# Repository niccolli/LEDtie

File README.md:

# About
Arduino remote controlling system from iPhone. Between iPhone and Arduino, there is a Node.js server. Communicating iPhone and Node.js on WebSocket, Node.js and Arduino on XBee.

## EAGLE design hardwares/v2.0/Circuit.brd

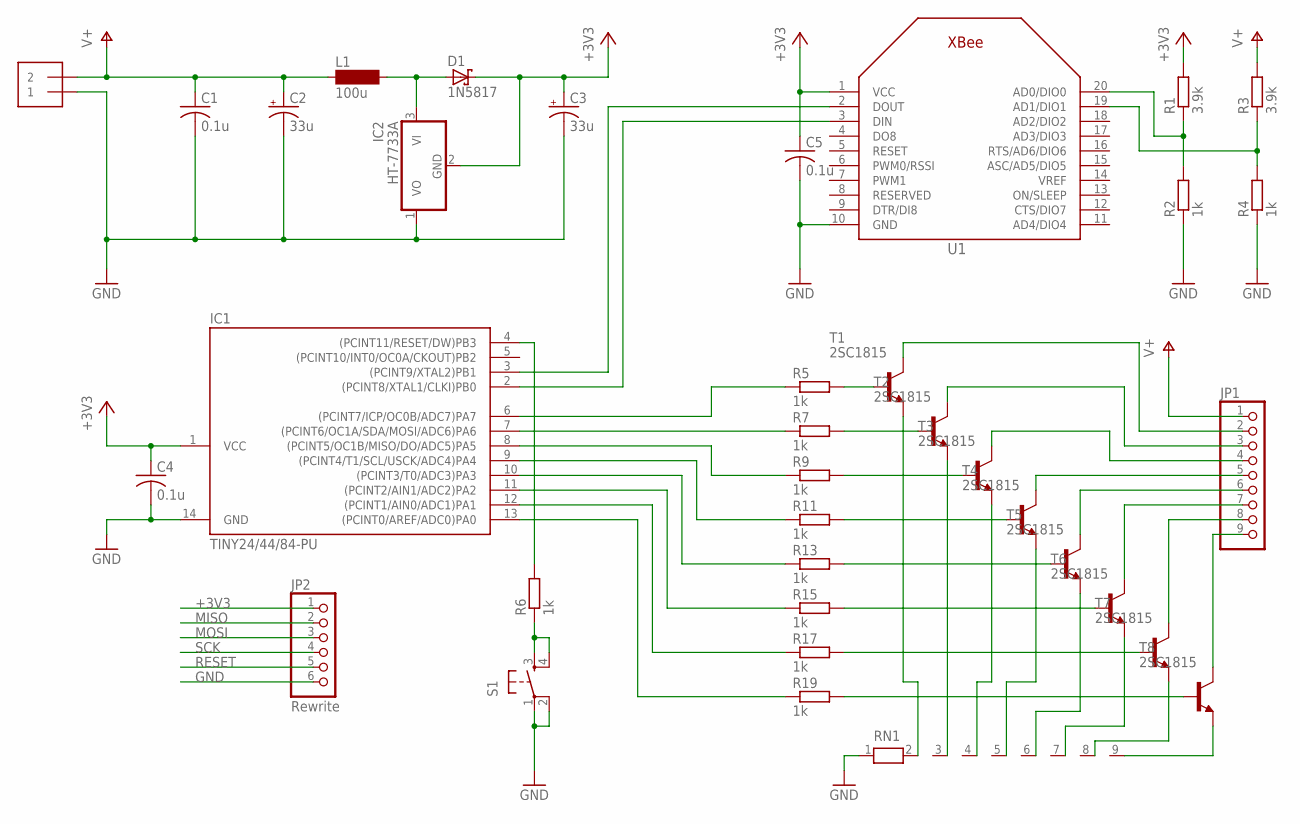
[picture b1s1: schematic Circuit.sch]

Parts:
C1, C4, C5: 0.1u; C050-025X075
C2, C3: 33u; E2,5-6
D1: 1N5817; DO41-7
IC1: TINY24/44/84-PU; DIL14
IC2: HT-7733A; TO92
J1: 1X2-3.5MM
JP1: PINHD-1X9; 1X09-BIG
JP2: Rewrite; 1X06
L1: 100u; BS11
R1, R3: 3.9k; 0204/7
R2, R4, R5, R6, R7, R9, R11, R13, R15, R17, R19: 1k; 0204/7
RN1: RN08; RN-9
S1: TAC_SWITCHPTH; TACTILE-PTH
T1, T2, T3, T4, T5, T6, T7, T8: 2SC1815; TO92-ECB
U1: XBEE

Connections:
+3V3: C3.+, C4.1, C5.1, D1.C, IC1.1 (VCC), IC2.2 (GND), JP2.1, R1.2, U1.1 (VCC)
GND: C1.2, C2.-, C3.-, C4.2, C5.2, IC1.14 (GND), IC2.1 (VO), J1.1, JP2.6, R2.1, R4.1, RN1.1, S1.1, S1.2, U1.10 (GND)
MISO: IC1.8 ((PCINT5/OC1B/MISO/DO/ADC5)PA5), JP2.2, R9.1
MOSI: IC1.7 ((PCINT6/OC1A/SDA/MOSI/ADC6)PA6), JP2.3, R7.1
unnamed: IC1.3 ((PCINT9/XTAL2)PB1), U1.2 (DOUT)
unnamed: IC1.2 ((PCINT8/XTAL1/CLKI)PB0), U1.3 (DIN)
unnamed: D1.A, IC2.3 (VI), L1.2
unnamed: R6.1, S1.3, S1.4
unnamed: R5.2, T1.B
unnamed: JP1.2, T1.C
unnamed: R1.1, R2.2, U1.20 (AD0/DIO0)
unnamed: R3.1, R4.2, U1.19 (AD1/DIO1)
unnamed: R7.2, T2.B
unnamed: JP1.3, T2.C
unnamed: IC1.6 ((PCINT7/ICP/OC0B/ADC7)PA7), R5.1
unnamed: R9.2, T3.B
unnamed: JP1.4, T3.C
unnamed: RN1.8, T7.E
unnamed: R11.2, T4.B
unnamed: JP1.5, T4.C
unnamed: R13.2, T5.B
unnamed: JP1.6, T5.C
unnamed: R15.2, T6.B
unnamed: JP1.7, T6.C
unnamed: IC1.10 ((PCINT3/T0/ADC3)PA3), R13.1
unnamed: R17.2, T7.B
unnamed: JP1.8, T7.C
unnamed: IC1.11 ((PCINT2/AIN1/ADC2)PA2), R15.1
unnamed: R19.2, T8.B
unnamed: JP1.9, T8.C
unnamed: IC1.12 ((PCINT1/AIN0/ADC1)PA1), R17.1
unnamed: RN1.3, T2.E
unnamed: RN1.4, T3.E
unnamed: RN1.5, T4.E
unnamed: RN1.6, T5.E
unnamed: RN1.7, T6.E
unnamed: RN1.9, T8.E
unnamed: RN1.2, T1.E
unnamed: IC1.13 ((PCINT0/AREF/ADC0)PA0), R19.1
RESET: IC1.4 ((PCINT11/RESET/DW)PB3), JP2.5, R6.2
SCK: IC1.9 ((PCINT4/T1/SCL/USCK/ADC4)PA4), JP2.4, R11.1
V+: C1.1, C2.+, J1.2, JP1.1, L1.1, R3.2

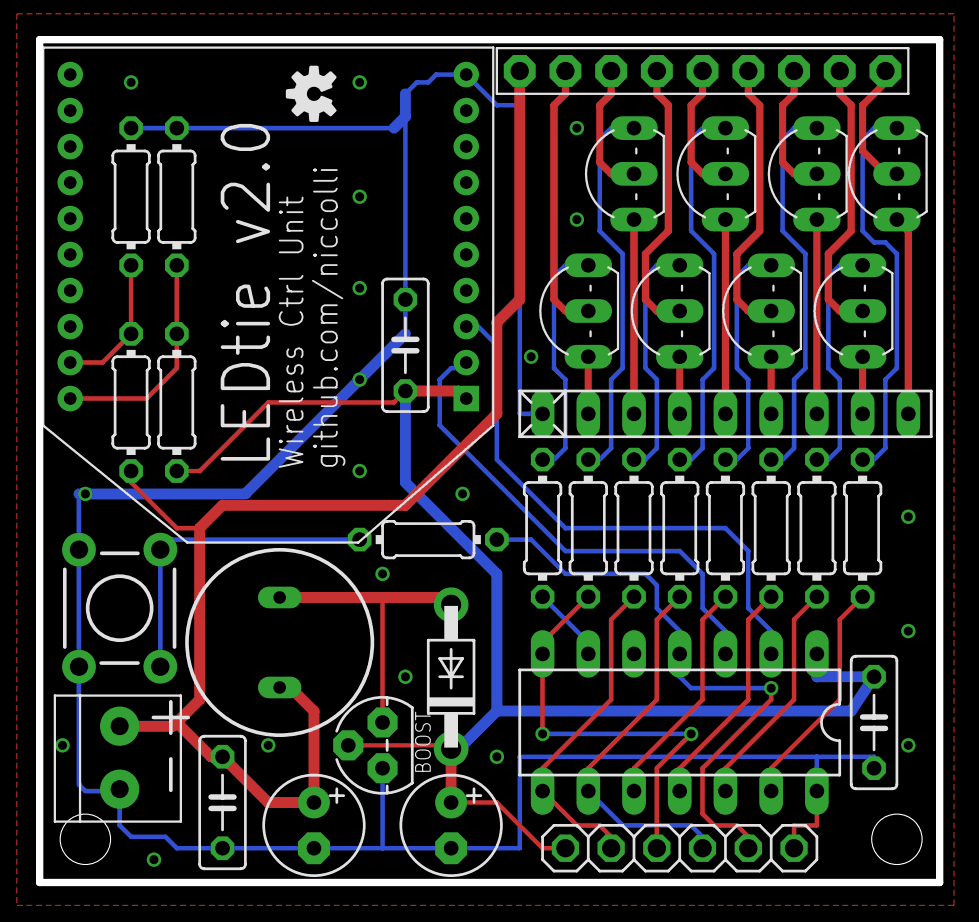
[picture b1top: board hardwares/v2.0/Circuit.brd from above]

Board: 2 copper layers, 50.0 x 46.8 mm, 37 parts (0 on the bottom side), 42 nets.

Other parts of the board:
U$1: OSHW-LOGO-S

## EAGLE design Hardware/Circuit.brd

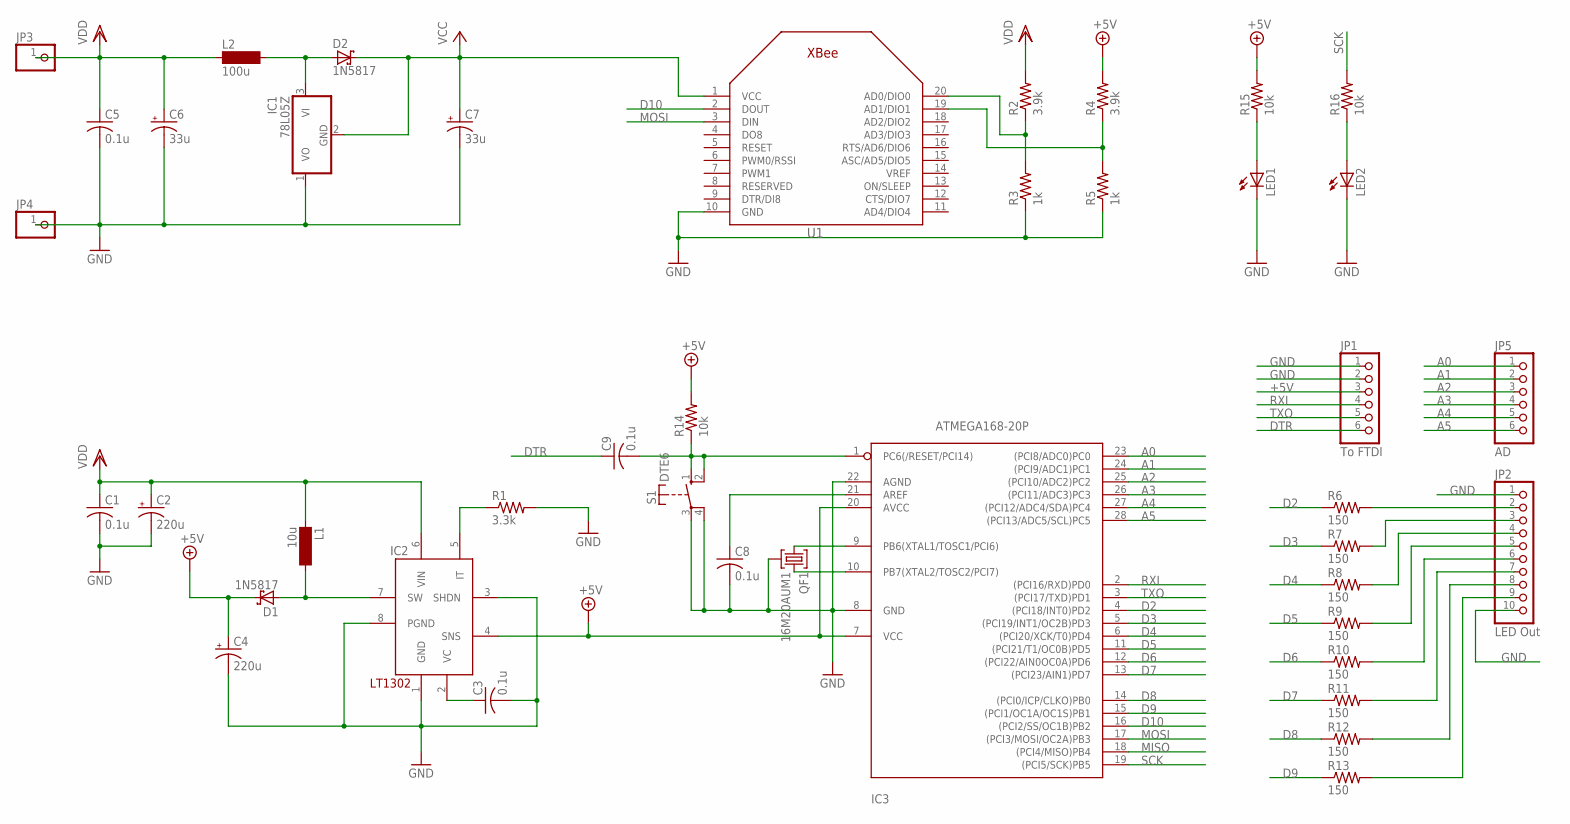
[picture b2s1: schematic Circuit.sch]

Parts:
C1, C3, C5, C8, C9: 0.1u; C050-025X075
C2, C4: 220u; E2,5-6
C6, C7: 33u; E2,5-5
D1: 1N5817; DO35-7
D2: 1N5817; DO41-10
IC1: 78L05Z; TO92
IC2: LT1302; DIL08
IC3: ATMEGA168-20P; DIL28-3
JP1: To FTDI; 1X06
JP2: LED Out; 1X10-BIG
JP3, JP4: PINHD-1X1; 1X01
JP5: AD; 1X06
L1: 10u; BS11
L2: 100u; BS11
LED1, LED2: LED3MM
QF1: 16M20AUM1; UM1
R1: 3.3k; 0204/7
R2, R4: 3.9k; 0207/7
R3, R5: 1k; 0207/7
R6, R7, R8, R9, R10, R11, R12, R13: 150; 0204/7
R14: 10k; 0204/7
R15, R16: 10k; 0207/7
S1: DTE6
U1: XBEE

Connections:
+5V: C4.+, D1.C, IC2.4 (SNS), IC3.7 (VCC), IC3.20 (AVCC), JP1.3, R4.2, R14.2, R15.2
A0: IC3.23 ((PCI8/ADC0)PC0), JP5.1
A1: IC3.24 ((PCI9/ADC1)PC1), JP5.2
A2: IC3.25 ((PCI10/ADC2)PC2), JP5.3
A3: IC3.26 ((PCI11/ADC3)PC3), JP5.4
A4: IC3.27 ((PCI12/ADC4/SDA)PC4), JP5.5
A5: IC3.28 ((PCI13/ADC5/SCL)PC5), JP5.6
D2: IC3.4 ((PCI18/INT0)PD2), R6.1
D3: IC3.5 ((PCI19/INT1/OC2B)PD3), R7.1
D4: IC3.6 ((PCI20/XCK/T0)PD4), R8.1
D5: IC3.11 ((PCI21/T1/OC0B)PD5), R9.1
D6: IC3.12 ((PCI22/AIN0OC0A)PD6), R10.1
D7: IC3.13 ((PCI23/AIN1)PD7), R11.1
D8: IC3.14 ((PCI0/ICP/CLKO)PB0), R12.1
D9: IC3.15 ((PCI1/OC1A/OC1S)PB1), R13.1
D10: IC3.16 ((PCI2/SS/OC1B)PB2), U1.2 (DOUT)
DTR: C9.1, JP1.6
GND: C1.2, C2.-, C3.2, C4.-, C5.2, C6.-, C7.-, C8.2, IC1.1 (VO), IC2.1 (GND), IC2.3 (SHDN), IC2.8 (PGND), IC3.8 (GND), IC3.22 (AGND), JP1.1, JP1.2, JP2.1, JP2.10, JP4.1, LED1.K (C), LED2.K (C), QF1.2, R1.2, R3.1, R5.1, S1.3, S1.4, U1.10 (GND)
MISO: IC3.18 ((PCI4/MISO)PB4)
MOSI: IC3.17 ((PCI3/MOSI/OC2A)PB3), U1.3 (DIN)
unnamed: C3.1, IC2.2 (VC)
unnamed: D1.A, IC2.7 (SW), L1.2
unnamed: R4.1, R5.2, U1.19 (AD1/DIO1)
unnamed: IC2.5 (IT), R1.1
unnamed: D2.A, IC1.3 (VI), L2.2
unnamed: C8.1, IC3.21 (AREF)
unnamed: IC3.9 (PB6(XTAL1/TOSC1/PCI6)), QF1.1
unnamed: IC3.10 (PB7(XTAL2/TOSC2/PCI7)), QF1.3
unnamed: R2.1, R3.2, U1.20 (AD0/DIO0)
unnamed: JP2.2, R6.2
unnamed: JP2.3, R7.2
unnamed: JP2.4, R8.2
unnamed: JP2.5, R9.2
unnamed: JP2.6, R10.2
unnamed: JP2.7, R11.2
unnamed: JP2.8, R12.2
unnamed: C9.2, IC3.1 (PC6(/RESET/PCI14)), R14.1, S1.1 (S), S1.2 (S)
unnamed: LED1.A, R15.1
unnamed: LED2.A, R16.1
unnamed: JP2.9, R13.2
RXI: IC3.2 ((PCI16/RXD)PD0), JP1.4
SCK: IC3.19 ((PCI5/SCK)PB5), R16.2
TXO: IC3.3 ((PCI17/TXD)PD1), JP1.5
VCC: C7.+, D2.C, IC1.2 (GND), U1.1 (VCC)
VDD: C1.1, C2.+, C5.1, C6.+, IC2.6 (VIN), JP3.1, L1.1, L2.1, R2.2

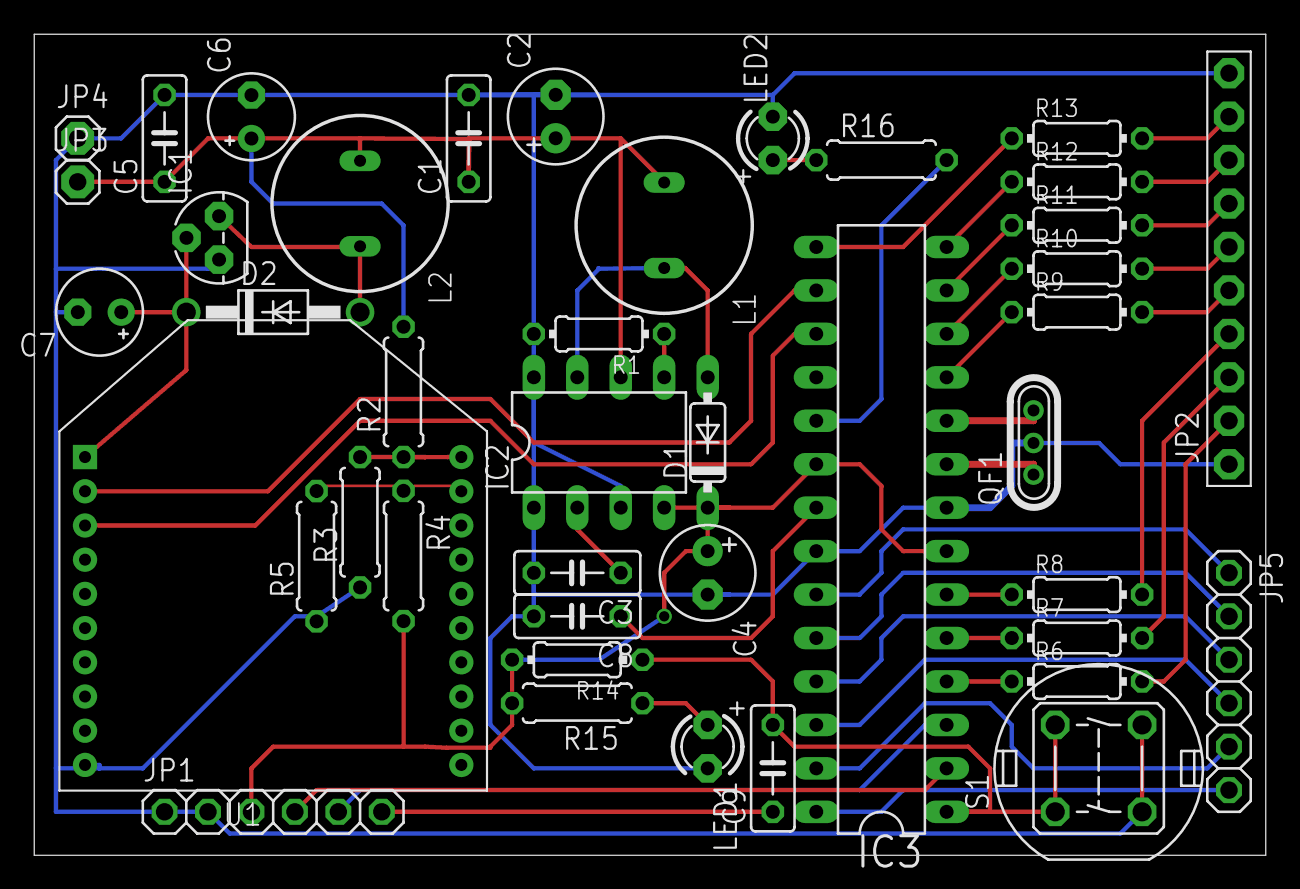
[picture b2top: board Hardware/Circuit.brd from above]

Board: 2 copper layers, 72.0 x 48.0 mm, 42 parts (0 on the bottom side), 44 nets.

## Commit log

2012-10-20 First commit: Arduino sketch
2012-10-20 First commit: WebSocket and XBee server
2012-10-20 README added
2012-10-21 Sketch: Use static variable
2012-10-21 Sketch fixed: Delete unused variables
2012-10-23 LEDtie.ino: Fixed state changing
2012-11-04 Changed for XBee API mode
2012-12-09 Adding pulse lighting
2012-12-09 Added circuit board design
2012-12-11 Power voltage of circuit board is changed
2012-12-11 Circuit: Add RESET sw
2012-12-12 Circuit: GND pattern changed
2012-12-13 Circuit: NPN Transistors changed
2012-12-13 Circuit fixed
2012-12-19 Circuit: Rewrite connector added

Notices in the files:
parts and their libraries:
SparkFun: Licensing: CC v3.0 Share-Alike You are welcome to use this library for commercial purposes.
